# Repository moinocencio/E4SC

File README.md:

# E4SC

**BLDC Motor Controller made for Electronics 4 Class**

This is a very simple project made for a curricular unit from Electronics and Telecommunications Engineering at Universidade de Aveiro.

The main initial contributors from this project are myself and luismof7 (https://github.com/luismof7), but any kind of feedback would be appreciated.

The motor controller tries to implement some basic functions, like max top speed, PWM control for speed maintenance, bluetooth control, ...

We hope to add more and more functionalities to the controller, to get to a point where it is a viable option to implement on a small RC plane (or something like that).

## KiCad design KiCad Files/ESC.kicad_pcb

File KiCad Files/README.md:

# PCB and Schematics

The current version of the controller has some functionalities implemented mainly for the University project, that don't have any use as of now.

The custom Footprints were made to adjust to our University CNC, but the PCB has the default Kicad footprints.

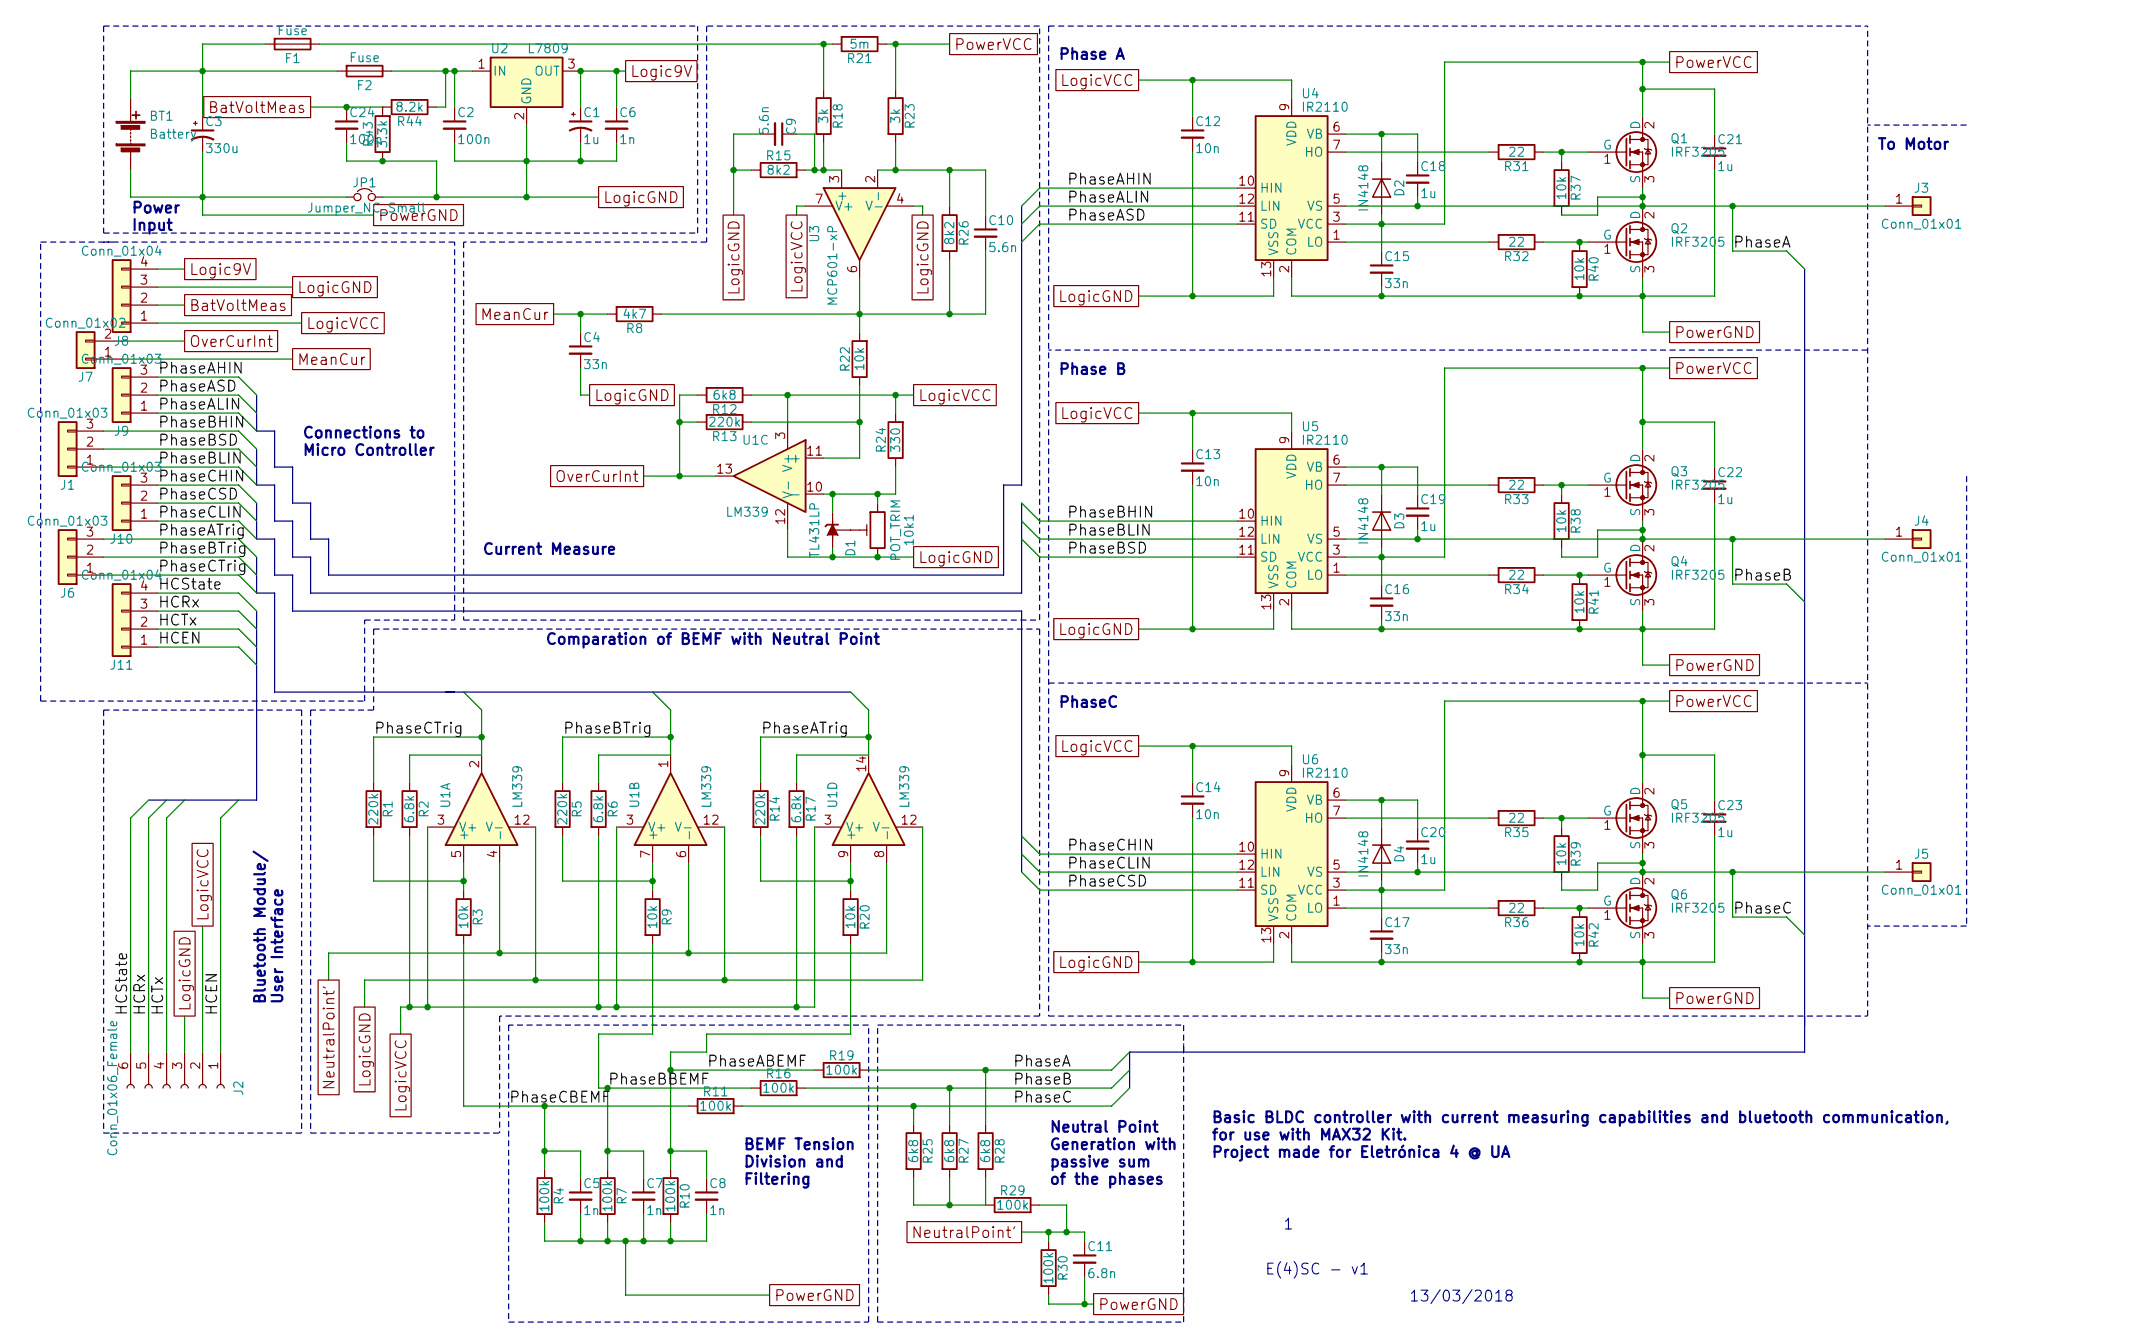
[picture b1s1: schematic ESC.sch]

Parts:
10k1: POT_TRIM; Potentiometer_WirePads_Small
BT1: Battery; WireConnection_2.50mmDrill_LargePad
C1: 1u; CP_Radial_D4.0mm_P2.00mm
C2, C24: 100n; C_1206_HandSoldering
C3: 330u; CP_Radial_D12.5mm_P7.50mm
C4, C15, C16, C17: 33n; C_1206_HandSoldering
C5, C6, C7, C8: 1n; C_1206_HandSoldering
C9, C10: 5.6n; C_1206_HandSoldering
C11: 6.8n; C_1206_HandSoldering
C12, C13, C14: 10n; C_1206_HandSoldering
C18, C19, C20: 1u; C_1206_HandSoldering
C21, C22, C23: 1u; C_Disc_D4.3mm_W1.9mm_P5.00mm
D1: TL431LP; TO-92_Inline_Narrow_Oval
D2, D3, D4: IN4148; D_DO-35_SOD27_P7.62mm_Horizontal
F1: Fuse; Fuseholder_ATO_Blade_littlefuse_Pudenz_2_Pin
F2: Fuse; Fuseholder5x20_horiz_open_inline_Type-I
J1, J6, J9, J10: Conn_01x03; Socket_Strip_Straight_1x03_Pitch2.54mm
J2: Conn_01x06_Female; Socket_Strip_Angled_1x06_Pitch2.54mm
J3, J4, J5: Conn_01x01; MountingHole_4.3mm_M4_Pad
J7: Conn_01x02; Socket_Strip_Straight_1x02_Pitch2.54mm
J8, J11: Conn_01x04; Socket_Strip_Straight_1x04_Pitch2.54mm
JP1: Jumper_NC_Small; CP_Tantalum_Case-A_EIA-3216-18_Hand
Q1, Q2, Q3, Q4, Q5, Q6: IRF3205; TO-220
R1, R5, R13, R14: 220k; R_1206_HandSoldering
R2, R6, R17: 6.8k; R_1206_HandSoldering
R3, R9, R20, R22, R37, R38, R39, R40, R41, R42: 10k; R_1206_HandSoldering
R4, R7, R10, R11, R16, R19, R29, R30: 100k; R_1206_HandSoldering
R8: 4k7; R_1206_HandSoldering
R12, R25, R27, R28: 6k8; R_1206_HandSoldering
R15, R26: 8k2; R_1206_HandSoldering
R18, R23: 3k; R_1206_HandSoldering
R21: 5m; R_Axial_Power_L25.0mm_W9.0mm_P30.48mm
R24: 330; R_1206_HandSoldering
R31, R32, R33, R34, R35, R36: 22; R_1206_HandSoldering
R43: 3.3k; R_1206_HandSoldering
R44: 8.2k; R_1206_HandSoldering
U1: LM339; DIP-14_W7.62mm_Socket
U2: L7809; TO-220-3_Vertical
U3: MCP601-xP; DIP-8_W7.62mm_Socket
U4, U5, U6: IR2110; DIP-14_W7.62mm

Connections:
/PhaseA: C18.2, J3.1, Q1.3 (S), Q2.2 (D), R19.2, R28.1, R37.2, U4.5 (VS)
/PhaseABEMF: C8.1, R10.1, R19.1, R20.2
/PhaseAHIN: J9.3, U4.10 (HIN)
/PhaseALIN: J9.1, U4.12 (LIN)
/PhaseASD: J9.2, U4.11 (SD)
/PhaseATrig: J6.3, R14.1, R17.1, U1.14
/PhaseB: C19.2, J4.1, Q3.3 (S), Q4.2 (D), R16.2, R27.1, R38.2, U5.5 (VS)
/PhaseBBEMF: C7.1, R7.1, R9.2, R16.1
/PhaseBHIN: J1.3, U5.10 (HIN)
/PhaseBLIN: J1.1, U5.12 (LIN)
/PhaseBSD: J1.2, U5.11 (SD)
/PhaseBTrig: J6.2, R5.1, R6.1, U1.1
/PhaseC: C20.2, J5.1, Q5.3 (S), Q6.2 (D), R11.2, R25.1, R39.2, U6.5 (VS)
/PhaseCBEMF: C5.1, R3.2, R4.1, R11.1
/PhaseCHIN: J10.3, U6.10 (HIN)
/PhaseCLIN: J10.1, U6.12 (LIN)
/PhaseCSD: J10.2, U6.11 (SD)
/PhaseCTrig: J6.1, R1.1, R2.1, U1.2
BatVoltMeas: C24.1, J8.2, R43.2, R44.2
Logic9V: C1.1, C6.1, J8.4, U2.3 (OUT)
LogicGND: 10k1.3, C1.2, C2.2, C4.2, C6.2, C9.2, C12.2, C13.2, C14.2, C24.2, D1.2 (A), J2.3, J8.3, JP1.2, R15.1, R43.1, U1.12 (V-), U2.2 (GND), U3.4 (V-), U4.13 (VSS), U5.13 (VSS), U6.13 (VSS)
LogicVCC: C12.1, C13.1, C14.1, J2.2, J8.1, R2.2, R6.2, R12.1, R17.2, R24.2, U1.3 (V+), U3.7 (V+), U4.9 (VDD), U5.9 (VDD), U6.9 (VDD)
MeanCur: C4.1, J7.1, R8.2
unnamed: 10k1.1, D1.3 (K), R24.1, U1.10 (-)
unnamed: 10k1.2, D1.1 (REF)
unnamed: BT1.1 (+), C3.1, F1.2, F2.2
unnamed: C2.1, F2.1, R44.1, U2.1 (IN)
unnamed: C9.1, R15.2, R18.2, U3.3 (+)
unnamed: C10.1, R23.2, R26.1, U3.2 (-)
unnamed: C10.2, R8.1, R22.2, R26.2, U3.6
unnamed: C18.1, D2.1 (K), U4.6 (VB)
unnamed: C19.1, D3.1 (K), U5.6 (VB)
unnamed: C20.1, D4.1 (K), U6.6 (VB)
unnamed: F1.1, R18.1, R21.2
unnamed: J2.1, J11.1
unnamed: J2.4, J11.2
unnamed: J2.5, J11.3
unnamed: J2.6, J11.4
unnamed: Q1.1 (G), R31.1, R37.1
unnamed: Q2.1 (G), R32.1, R40.1
unnamed: Q3.1 (G), R33.1, R38.1
unnamed: Q4.1 (G), R34.1, R41.1
unnamed: Q5.1 (G), R35.1, R39.1
unnamed: Q6.1 (G), R36.1, R42.1
unnamed: R1.2, R3.1, U1.5 (+)
unnamed: R5.2, R9.1, U1.7 (+)
unnamed: R13.1, R22.1, U1.11 (+)
unnamed: R14.2, R20.1, U1.9 (+)
unnamed: R25.2, R27.2, R28.2, R29.1
unnamed: R31.2, U4.7 (HO)
unnamed: R32.2, U4.1 (LO)
unnamed: R33.2, U5.7 (HO)
unnamed: R34.2, U5.1 (LO)
unnamed: R35.2, U6.7 (HO)
unnamed: R36.2, U6.1 (LO)
NeutralPoint': C11.1, R29.2, R30.1, U1.4 (-), U1.6 (-), U1.8 (-)
OverCurInt: J7.2, R12.2, R13.2, U1.13
PowerGND: BT1.2 (-), C3.2, C5.2, C7.2, C8.2, C11.2, C15.2, C16.2, C17.2, C21.2, C22.2, C23.2, JP1.1, Q2.3 (S), Q4.3 (S), Q6.3 (S), R4.2, R7.2, R10.2, R30.2, R40.2, R41.2, R42.2, U4.2 (COM), U5.2 (COM), U6.2 (COM)
PowerVCC: C15.1, C16.1, C17.1, C21.1, C22.1, C23.1, D2.2 (A), D3.2 (A), D4.2 (A), Q1.2 (D), Q3.2 (D), Q5.2 (D), R21.1, R23.1, U4.3 (VCC), U5.3 (VCC), U6.3 (VCC)

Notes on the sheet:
E(4)SC - v1
13/03/2018
Power Input
Phase A
Phase B
PhaseC
Connections to Micro Controller
To Motor
Bluetooth Module/ User Interface
Neutral Point Generation with passive sum of the phases
BEMF Tension Division and Filtering
Comparation of BEMF with Neutral Point
Current Measure
Basic BLDC controller with current measuring capabilities and bluetooth communication, for use with MAX32 Kit. Project made for Eletrónica 4 @ UA

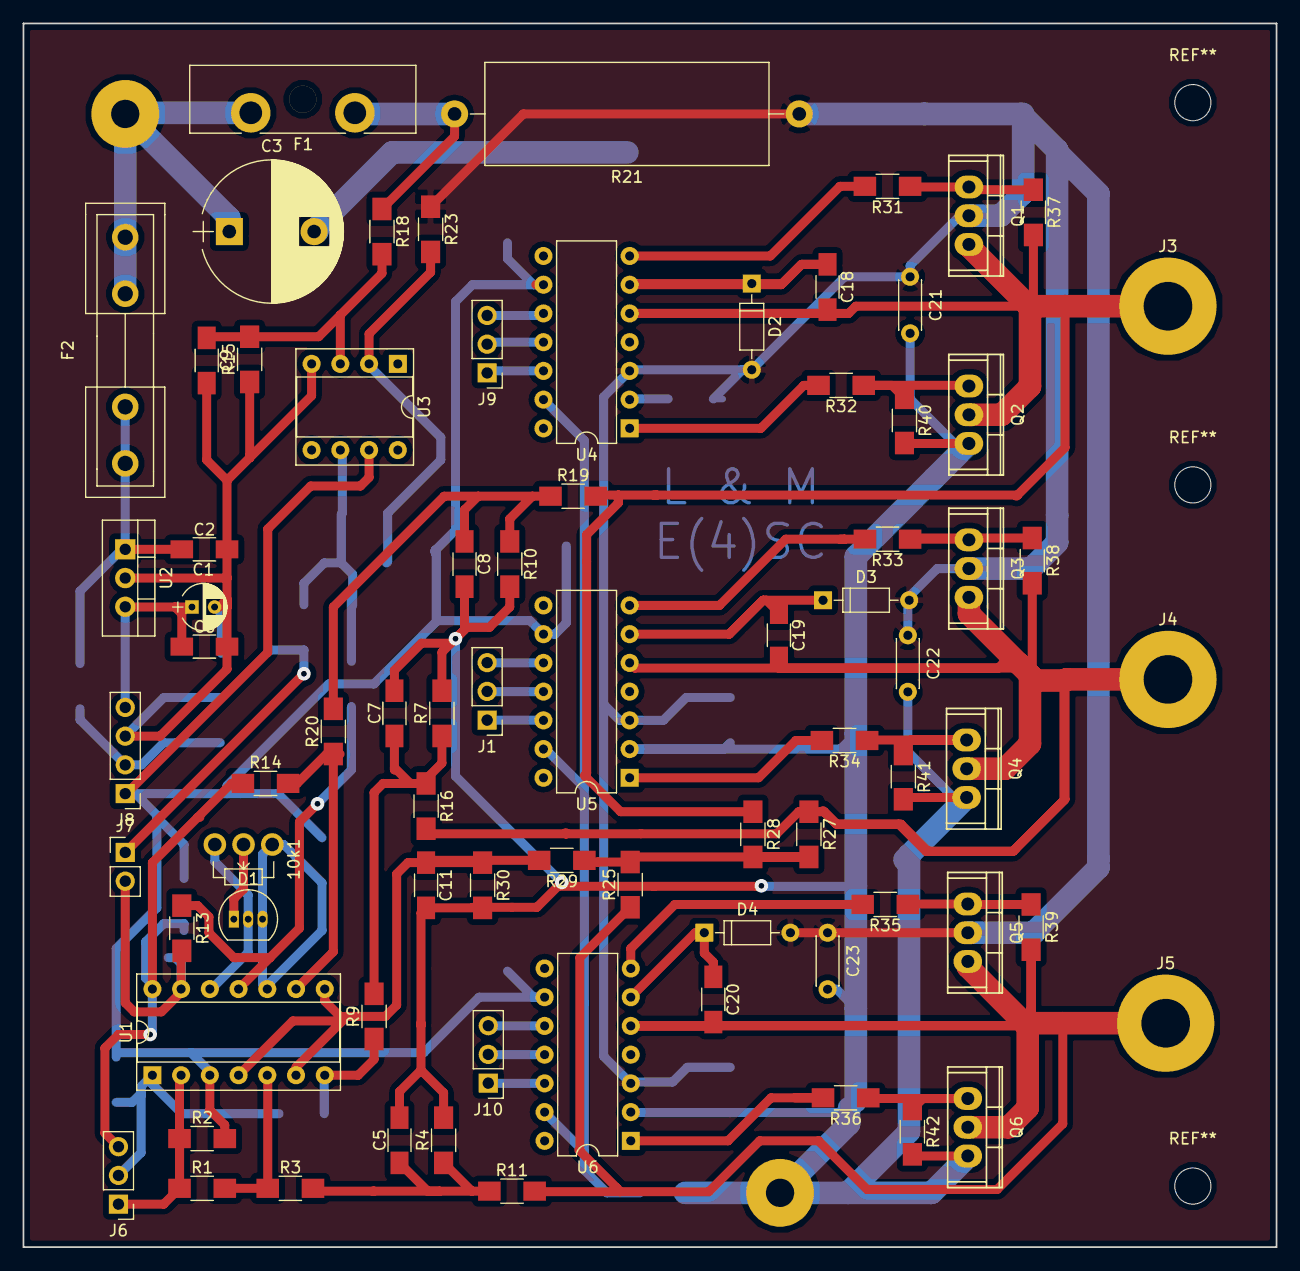
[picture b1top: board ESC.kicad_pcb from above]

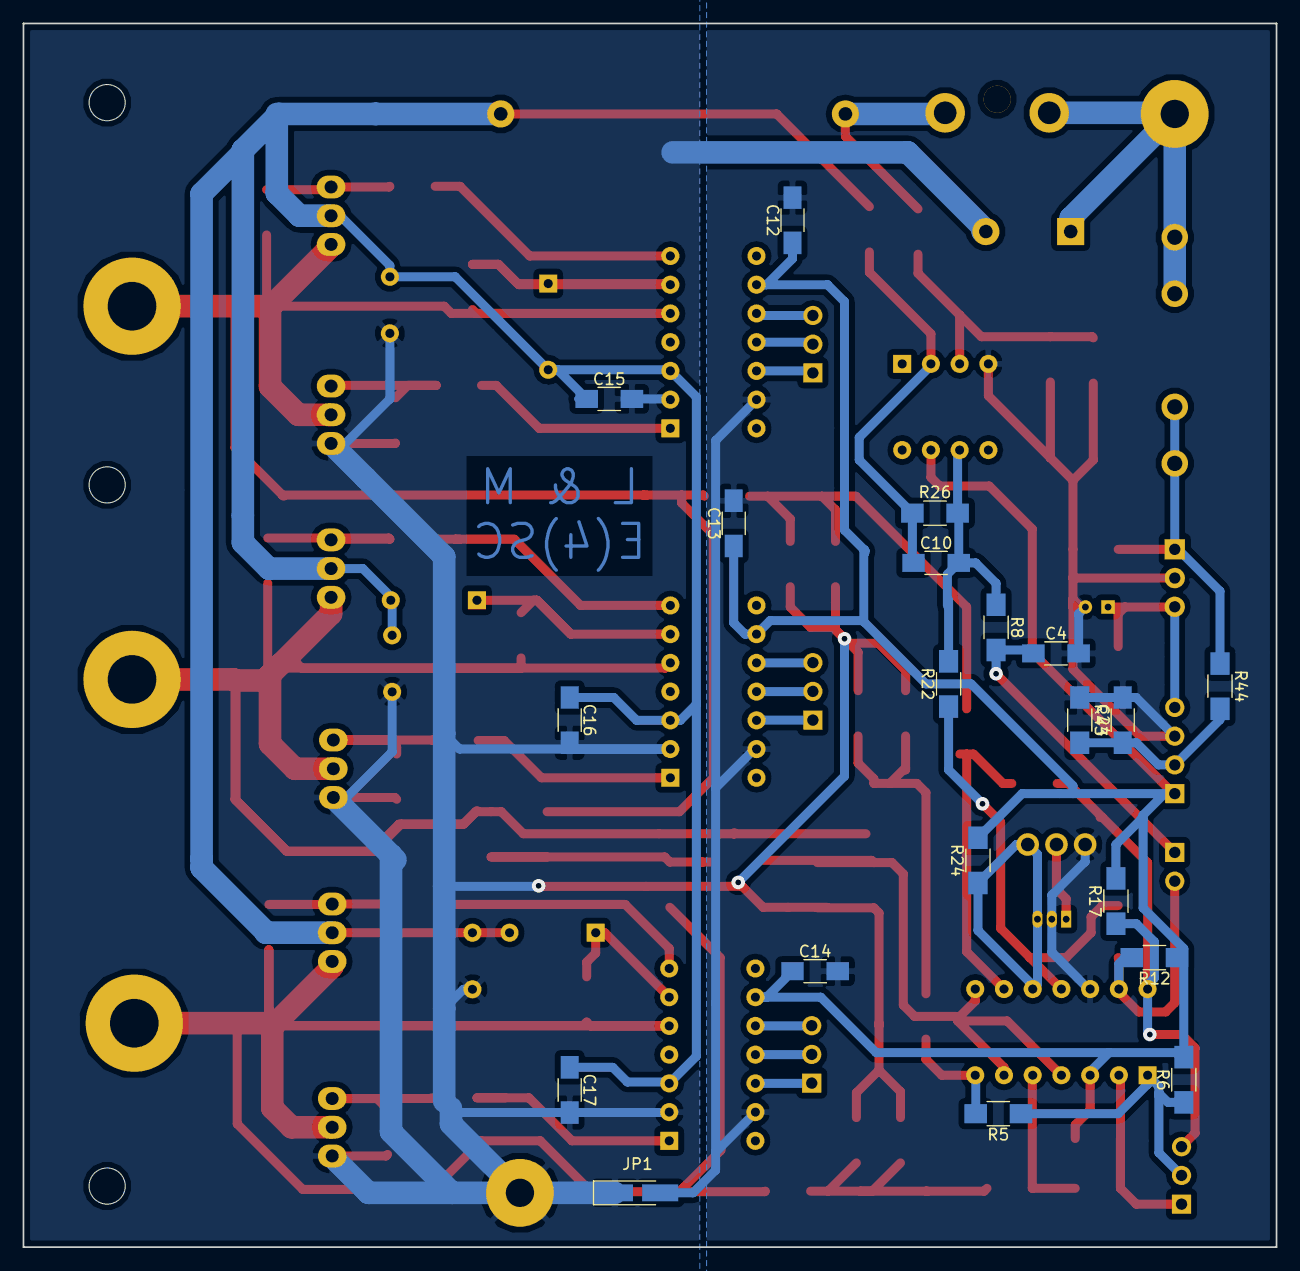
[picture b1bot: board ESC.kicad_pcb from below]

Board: 2 copper layers, 110.8 x 108.2 mm, 98 parts (20 on the bottom side), 55 nets.

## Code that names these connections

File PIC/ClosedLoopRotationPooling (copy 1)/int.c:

#include <stdio.h>
#include <stdlib.h>
#include <xc.h>
#include <sys/attribs.h> 

#include "int.h"

void enableInterrupts() // Enable System Interrupts
{
 
    // Problem 
    INTCONSET = _INTCON_MVEC_MASK;    
    // INTCONbits.MVEC = 1;
    __builtin_enable_interrupts(); 
}

void disableInterrupts() // Disable System Interrupts
{
    __builtin_disable_interrupts(); 
}

void config_adcInt() // Configuração das Interrupções
{
    // ADC Interrupt
    IPC6bits.AD1IP = 2;     // Priority
	IEC1bits.AD1IE = 1;     // Enable
	IFS1bits.AD1IF = 0;     // Reset AD1IF flag
}

void config_extInt1() // OverCurInt - pin 2
{
    IEC0bits.INT1IE = 0;    
    INTCONbits.INT1EP = 1;  // Rising Edge 
    IPC1bits.INT1IP = 6;    // Priority 
    IEC0bits.INT1IE = 1;    // Enable
    IFS0bits.INT1IF = 0;    // Reset Flag
}

void config_extInt2() // External Interrupt 2 - PhaseATrig - pin 7
{
    IEC0bits.INT2IE = 0;
    INTCONbits.INT2EP = 1;  // Rising Edge
    IPC2bits.INT2IP = 5;    // Priority 
    IEC0bits.INT2IE = 1;    // Enable
    IFS0bits.INT2IF = 0;    // Reset Flag
}

void config_extInt3() // External Interrupt 3 - PhaseBTrig - pin 21
{
    IEC0bits.INT3IE = 0;
    INTCONbits.INT3EP = 1;  // Rising Edge
    IPC3bits.INT3IP = 5;    // Priority 
    IEC0bits.INT3IE = 1;    // Enable
    IFS0bits.INT3IF = 0;    // Reset Flag
}

void config_extInt4() // External Interrupt 4 - PhaseCTrig - pin 20
{
    IEC0bits.INT4IE = 0;
    INTCONbits.INT4EP = 0;  // Falling Edge
    IPC4bits.INT4IP = 5;    // Priority 
    IEC0bits.INT4IE = 1;    // Enable
    IFS0bits.INT4IF = 0;    // Reset Flag
}

void config_Inttimer2() // PWM HIGH
{
    IPC2bits.T2IP = 1;      
    IEC0bits.T2IE = 1;      // Set Timer 2 Interrupt Enable bit 
}

void config_Inttimer3() // PWM LOW
{
    IPC3bits.T3IP = 1;
    IEC0bits.T3IE = 1;      // Set Timer 2 Interrupt Enable bit 
}

void config_Inttimer5() // Sequence Control
{
    IPC5bits.T5IP = 5;      
    IEC0bits.T5IE = 1;      /* Set Timer 5 Interrupt Enable bit */
}

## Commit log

2018-04-17 Base Files Added
2018-04-23 First version ADC
2018-04-23 UART and Configbits
2018-04-24 uptates adc-pwm-uart
2018-04-30 Updated v1 of PCB
2018-05-01 Finished PCB v1 and Started v2
2018-05-08 Code uptate
2018-05-08 Added PCB v2 and reorganized code
2018-05-08 correction
2018-05-08 Added pseudo code documentation
2018-05-09 Updated PseudoCode
2018-05-09 timers
2018-05-11 Added final PCB
2018-05-14 Phase 2 - update
2018-05-14 Phase 2 files
2018-05-15 timers and adc update
2018-05-15 Open Loop Shifter
2018-05-22 Update PCB and Phase 2
2018-05-26 Started 2TimerPWM
2018-05-28 1st iteration of closed loop rotation
2018-05-29 1st Scripts of closed loop rotations
2018-06-11 Final docs added
2018-06-22 Clean Repo
2018-06-22 Cleaned repo for sure
